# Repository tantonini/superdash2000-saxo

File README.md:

# superdash2000-saxo
Additional dashboard for Citroen Saxo with Arduino Nano Every

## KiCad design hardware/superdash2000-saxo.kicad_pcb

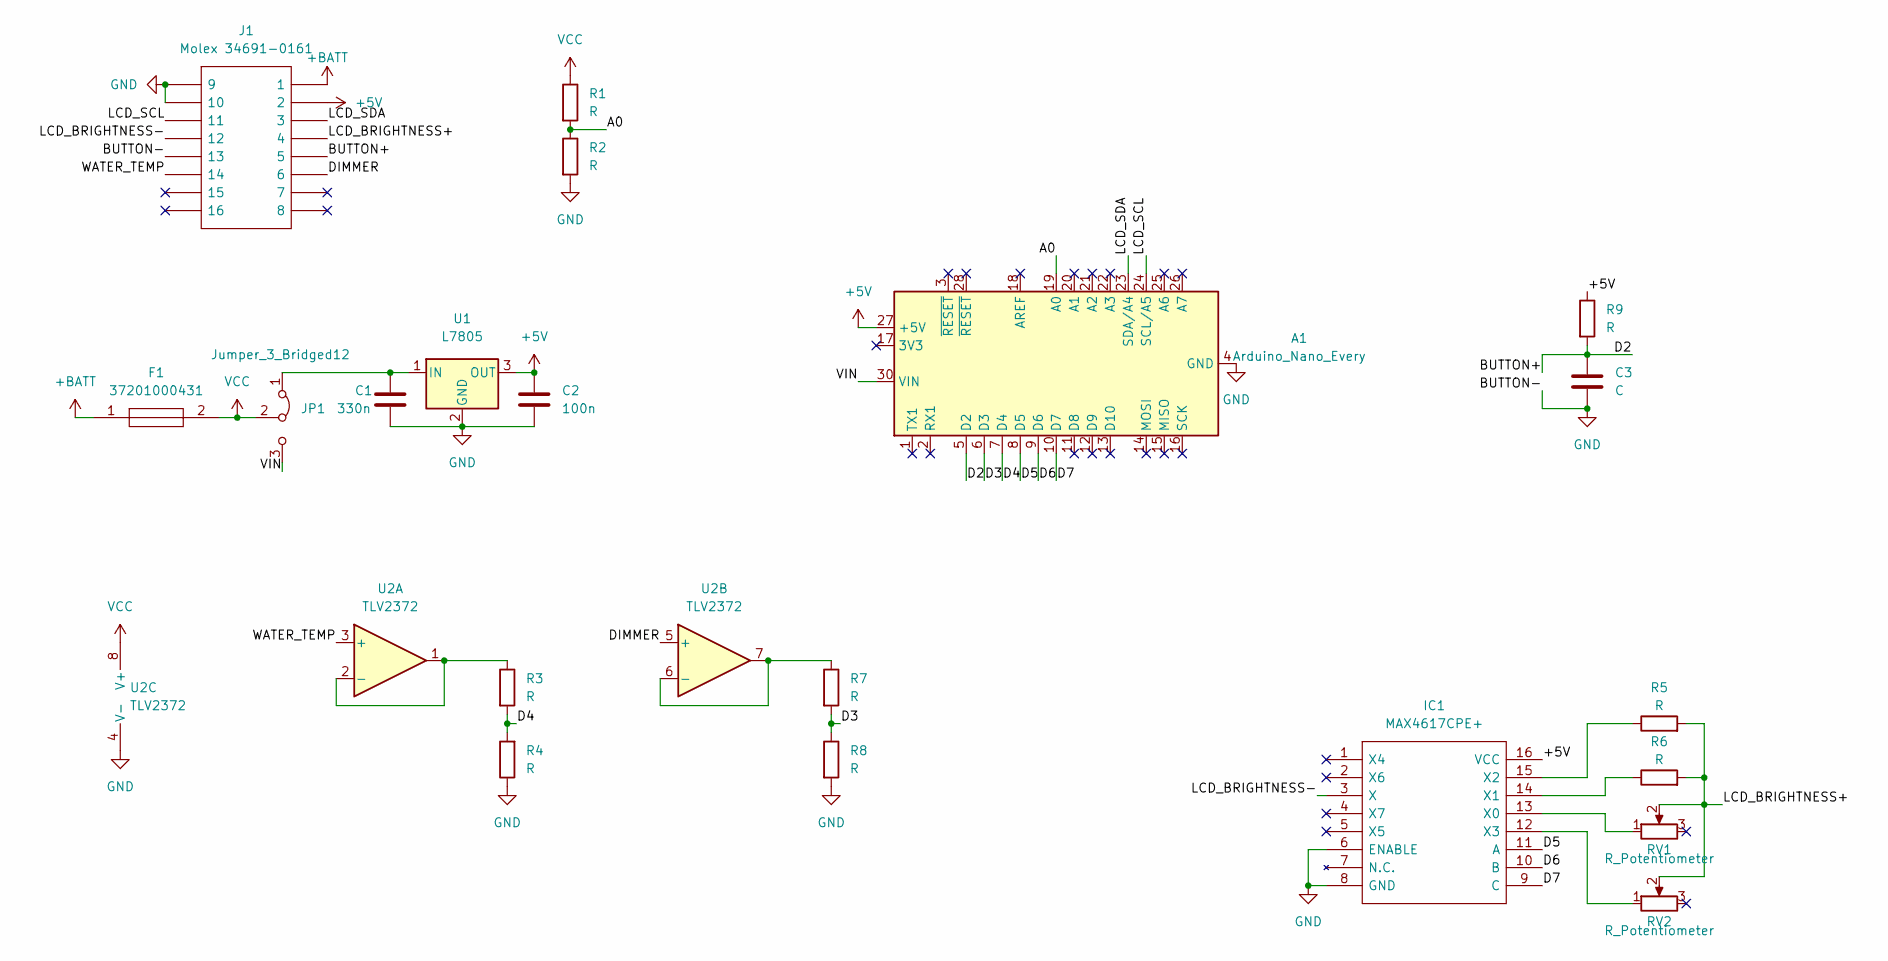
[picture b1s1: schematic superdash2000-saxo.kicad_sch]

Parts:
A1: Arduino_Nano_Every
C1: 330n; C_Disc_D5.0mm_W2.5mm_P2.50mm
C2: 100n; C_Disc_D5.0mm_W2.5mm_P2.50mm
C3: C; C_Disc_D5.0mm_W2.5mm_P2.50mm
F1: 37201000431; Mouser Part Number 576-37201000431
IC1: MAX4617CPE+; DIP-16_W7.62mm; Mouser Part Number 700-MAX4617CPE
J1: Molex 34691-0161; Mouser Part Number 538-34691-0161
JP1: Jumper_3_Bridged12; PinHeader_1x03_P2.54mm_Vertical
R1, R2, R3, R4, R5, R6, R7, R8, R9: R; R_Axial_DIN0207_L6.3mm_D2.5mm_P7.62mm_Horizontal
RV1, RV2: R_Potentiometer; Potentiometer_Bourns_3296W_Vertical
U1: L7805; TO-220-3_Vertical
U2: TLV2372; DIP-8_W7.62mm

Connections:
+5V: A1.27 (+5V), C2.1, IC1.16 (VCC), J1.2, R9.1, U1.3 (OUT)
+BATT: F1.1, J1.1
/A0: A1.19 (A0), R1.2, R2.1
/BUTTON+: A1.5 (D2), C3.1, J1.5, R9.2
/D3: A1.6 (D3), R7.2, R8.1
/D4: A1.7 (D4), R3.2, R4.2
/D5: A1.8 (D5), IC1.11 (A)
/D6: A1.9 (D6), IC1.10 (B)
/D7: A1.10 (D7), IC1.9 (C)
/DIMMER: J1.6, U2.5 (+)
/LCD_BRIGHTNESS+: J1.4, R5.2, R6.2, RV1.2, RV2.2
/LCD_BRIGHTNESS-: IC1.3 (X), J1.12
/LCD_SCL: A1.24 (SCL/A5), J1.11
/LCD_SDA: A1.23 (SDA/A4), J1.3
/VIN: A1.30 (VIN), JP1.3 (B)
/WATER_TEMP: J1.14, U2.3 (+)
GND: A1.4 (GND), A1.29 (GND), C1.2, C2.2, C3.2, IC1.6 (ENABLE), IC1.8 (GND), J1.9, J1.10, J1.13, R2.2, R4.1, R8.2, U1.2 (GND), U2.4 (V-)
unnamed: C1.1, JP1.1 (A), U1.1 (IN)
unnamed: IC1.12 (X3), RV2.1
unnamed: IC1.13 (X0), RV1.1
unnamed: IC1.14 (X1), R6.1
unnamed: IC1.15 (X2), R5.1
unnamed: R3.1, U2.1, U2.2 (-)
unnamed: R7.1, U2.6 (-), U2.7
VCC: F1.2, JP1.2 (C), R1.1, U2.8 (V+)

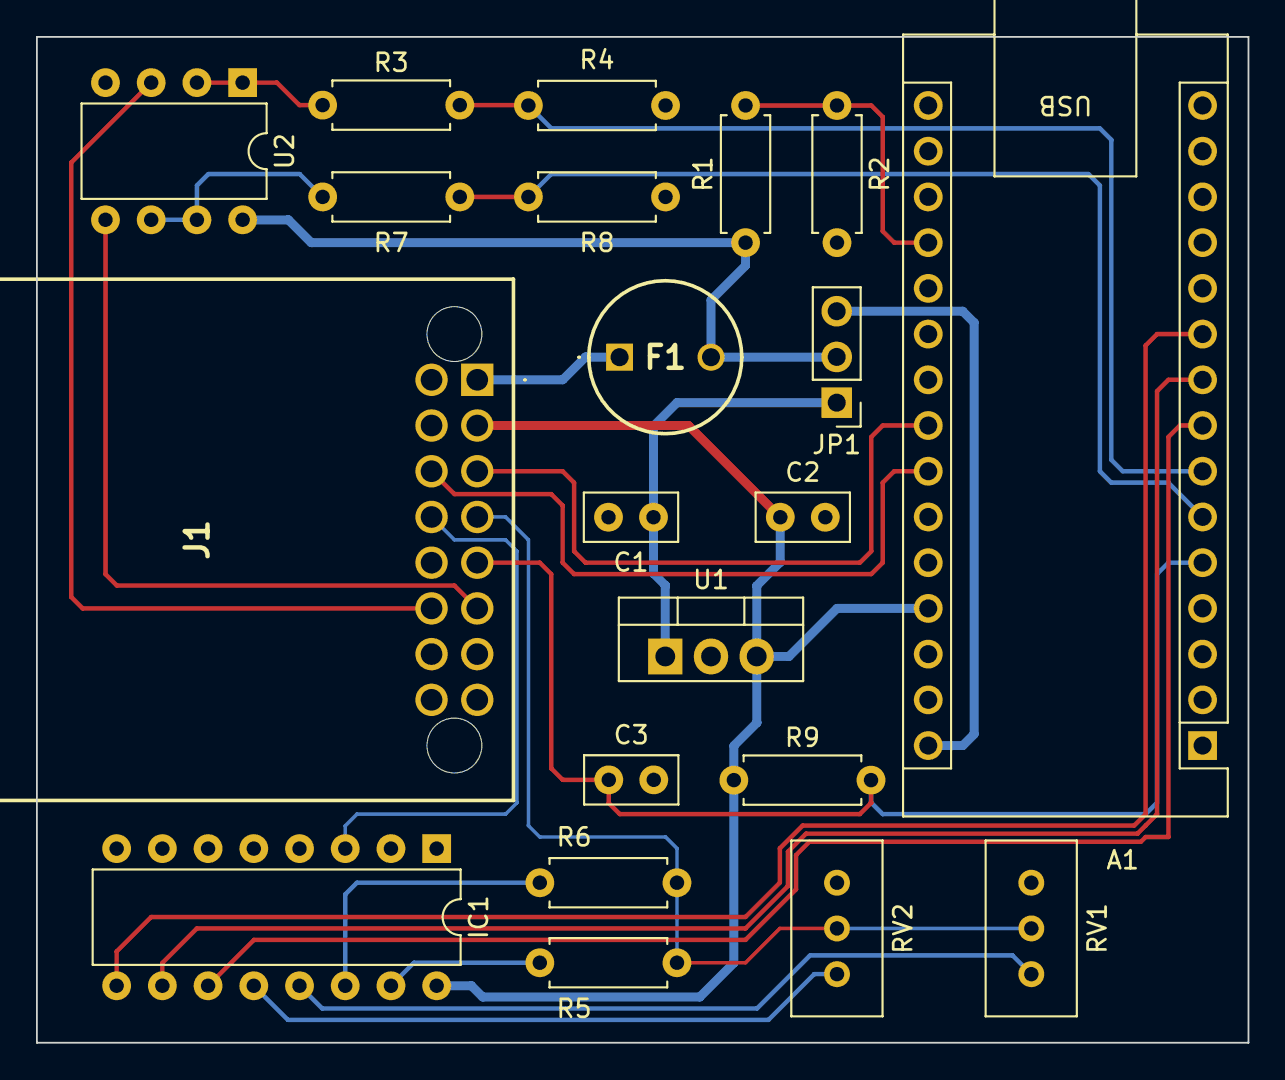
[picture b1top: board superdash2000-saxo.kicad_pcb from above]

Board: 2 copper layers, 67.3 x 55.9 mm, 21 parts (0 on the bottom side), 25 nets.

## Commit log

2022-03-02 Add new arduino project
2022-03-05 Initialize LCD display
2022-03-05 Add welcome screen
2022-03-05 Configure serial
2022-03-05 Add LCD refresh period
2022-03-05 Add lcd char degree
2022-03-05 Add mode management
2022-03-05 Configure ADC
2022-03-05 Add loop period
2022-03-05 Add battery mode
2022-03-05 Add push button with its irq handler
2022-03-05 Add char_full and char_empty
2022-03-06 Add config_water_temp_debug
2022-03-06 Move water duty cycle in mode instead of IRQ
    Calculating duty cucle in IRQ consumes useless 35us
2022-03-06 Add water temperature mode
2022-03-06 Move welcome screen after interrupts
    Permits to get data for water temp and being able to calculate
    it at the first loop iteration
2022-03-06 Prepare code for mode water temp 2
2022-03-06 Add water mode 2 (temp + bar)
2022-03-06 Change button to pull-up resistor
    Will permit to use a RC debouncer
2022-12-13 Add firmware folder
2022-12-18 Add kicad .gitignore
2022-12-23 hw: Add schematics draft
2023-01-22 hardware: Add LDO and modify PCB
2023-02-11 hardware: Add lib for Molex 34691-0161
2023-02-11 hardware: Update schematics
    Add fuse
    Add 3-pin jumper
    Add molex connector
    Move symbols position
2023-02-12 hardware: Update schematics
    VCC -> +BATT
    Add +5V label
    Add LCD-SCL label
    Add LCD-SDA label
2023-02-13 hardware: Add lcd potentiometer
2023-02-13 hardware: Rename LCD-Sxx to LCD_Sxx
2023-02-13 hardware: Move +BATT after fuse
2023-02-13 hardware: Add voltage divider for battery measurement
2023-02-22 hardware: Add water temp signal with opamp + voltage divider
2023-02-22 hardware: Add symbol for MCP4151-103E_P
2023-02-22 hardware: s/LCD_R/LCD_BRIGHTNESS + fix pin used on pot
2023-02-25 hardware: Add MAX4617CPE+ to lib
    Multiplexer
2023-02-25 hardware: Replace lcd brightness pot by mux
2023-02-25 hardware: Replace 2 R LCD brigthness by pots
2023-02-25 hardware: Add dimmer
2023-02-25 hardware: Fix annotations
2023-02-25 hardware: Add missing DIMMER label on connector
2023-02-25 hardware: Add no-connection on unused pins
2023-02-25 hardware: Add button
2023-02-25 hardware: Move connector + change power labels
2023-02-25 hardware: Fix fuse
    Fuse wasn't wired
2023-02-25 hardware: Move labels
2023-02-25 hardware: Split LDO and MCU
2023-02-25 hardware: Move opamp
2023-02-25 hardware: Split bat voltage divider and mcu
2023-02-25 hardware: Update footprints
2023-02-25 hardware: Add fuse lib
2023-02-25 hardware: Modify fuse with one added in lib
2023-02-25 hardware: Update molex connector 3d
2023-02-25 hardware: Place components on pcb
2023-02-25 hardware: Add arduino nano every fp + 3d
2023-02-25 hardware: Update arduino footprint
2023-02-25 hardware: Update pcb
2023-02-25 hardware: Add ground plane
2023-02-26 hardware: Invert LCD_BRIGHTNESS+/-
2023-02-26 hardware: Add arduino nano every without holes
2023-02-26 hardware: Change arduino footprint to without holes
2023-02-26 hardare: Update pcb
